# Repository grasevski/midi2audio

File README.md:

# midiguitar
Guitar midi controller + audio interface using an STM32H743ZI

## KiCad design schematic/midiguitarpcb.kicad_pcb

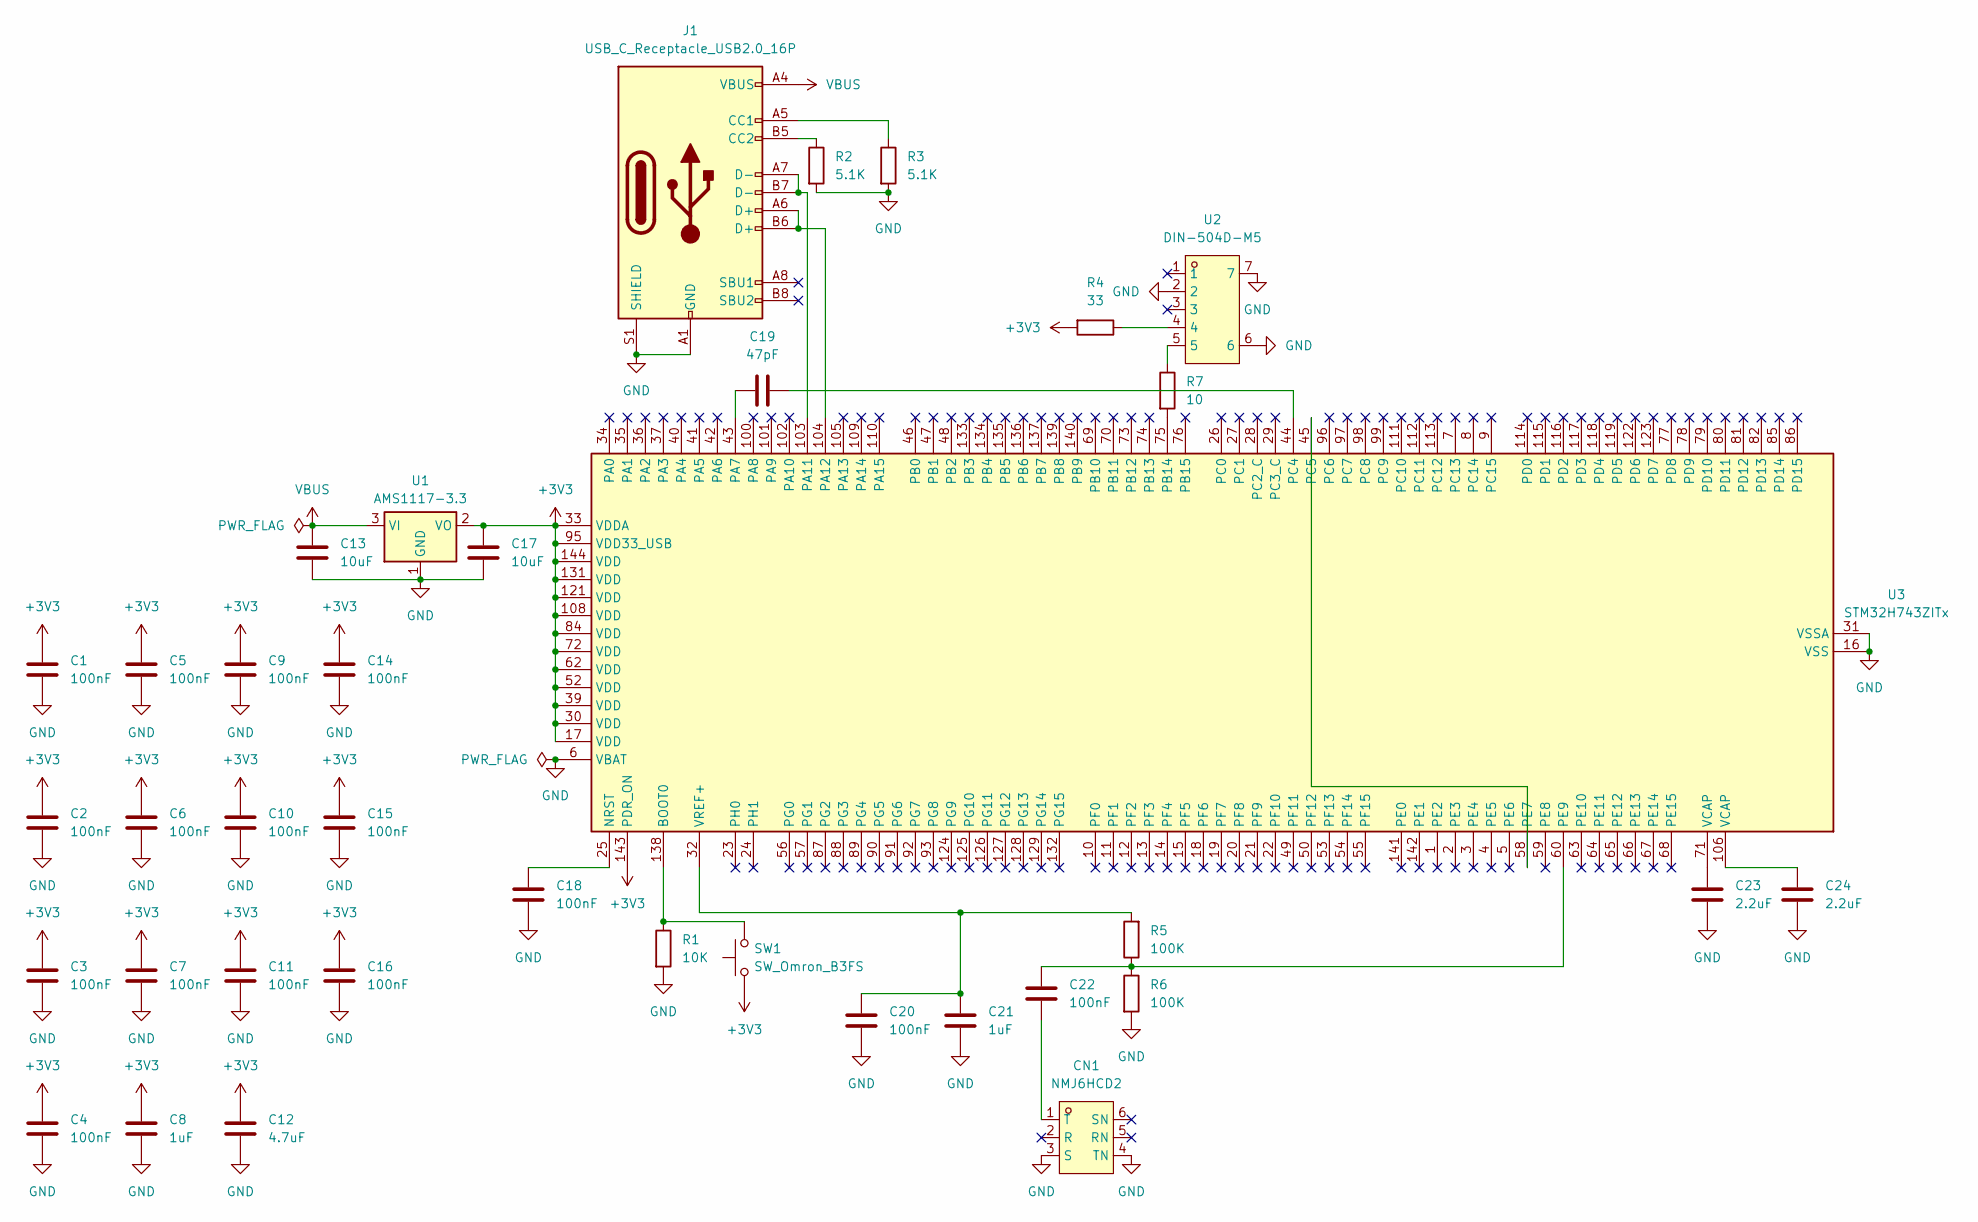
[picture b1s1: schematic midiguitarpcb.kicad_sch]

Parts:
C1, C2, C3, C4, C5, C6, C7, C9, C10, C11, C14, C15, C16, C18, C20, C22: 100nF; C_0402_1005Metric
C8, C21: 1uF; C_0402_1005Metric
C12: 4.7uF; C_0402_1005Metric
C13, C17: 10uF; C_0402_1005Metric
C19: 47pF; C_0402_1005Metric
C23, C24: 2.2uF; C_0402_1005Metric
CN1: NMJ6HCD2; AUDIO-TH_NMJ6HCD2; LCSC Part C368502
J1: USB_C_Receptacle_USB2.0_16P; USB_C_Receptacle_HRO_TYPE-C-31-M-12
R1: 10K; R_0402_1005Metric
R2, R3: 5.1K; R_0402_1005Metric
R4: 33; R_0402_1005Metric
R5, R6: 100K; R_0402_1005Metric
R7: 10; R_0402_1005Metric
SW1: SW_Omron_B3FS; SW_SPST_Omron_B3FS-100xP
U1: AMS1117-3.3; SOT-223-3_TabPin2
U2: DIN-504D-M5; CONN-TH_DIN-504D-M5; LCSC Part C2939347
U3: STM32H743ZITx; LQFP-144_20x20mm_P0.5mm

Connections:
+3V3: C1.1, C2.1, C3.1, C4.1, C5.1, C6.1, C7.1, C8.1, C9.1, C10.1, C11.1, C12.1, C14.1, C15.1, C16.1, C17.1, R4.2, SW1.1, U1.2 (VO), U3.17 (VDD), U3.30 (VDD), U3.33 (VDDA), U3.39 (VDD), U3.52 (VDD), U3.62 (VDD), U3.72 (VDD), U3.84 (VDD), U3.95 (VDD33_USB), U3.108 (VDD), U3.121 (VDD), U3.131 (VDD), U3.143 (PDR_ON), U3.144 (VDD)
GND: C1.2, C2.2, C3.2, C4.2, C5.2, C6.2, C7.2, C8.2, C9.2, C10.2, C11.2, C12.2, C13.2, C14.2, C15.2, C16.2, C17.2, C18.2, C20.2, C21.2, C23.2, C24.2, CN1.3 (S), CN1.4 (TN), J1.A1 (GND), J1.A12 (GND), J1.B1 (GND), J1.B12 (GND), J1.S1 (SHIELD), R1.2, R2.2, R3.2, R6.2, U1.1 (GND), U2.2, U2.6, U2.7, U3.6 (VBAT), U3.16 (VSS), U3.31 (VSSA), U3.38 (VSS), U3.51 (VSS), U3.61 (VSS), U3.83 (VSS), U3.94 (VSS), U3.107 (VSS), U3.120 (VSS), U3.130 (VSS)
unnamed: C23.1, U3.71 (VCAP)
unnamed: C24.1, U3.106 (VCAP)
unnamed: C22.1, CN1.1 (T)
unnamed: J1.A5 (CC1), R3.1
unnamed: J1.B5 (CC2), R2.1
unnamed: R4.1, U2.4
unnamed: R7.1, U2.5
unnamed: R1.1, SW1.2, U3.138 (BOOT0)
unnamed: C18.1, U3.25 (NRST)
unnamed: C19.1, U3.43 (PA7)
unnamed: J1.A7 (D-), J1.B7 (D-), U3.103 (PA11)
unnamed: J1.A6 (D+), J1.B6 (D+), U3.104 (PA12)
unnamed: R7.2, U3.75 (PB14)
unnamed: C19.2, U3.44 (PC4)
unnamed: U3.45 (PC5), U3.58 (PE7)
unnamed: C22.2, R5.1, R6.1, U3.60 (PE9)
unnamed: C20.1, C21.1, R5.2, U3.32 (VREF+)
VBUS: C13.1, J1.A4 (VBUS), J1.A9 (VBUS), J1.B4 (VBUS), J1.B9 (VBUS), U1.3 (VI)

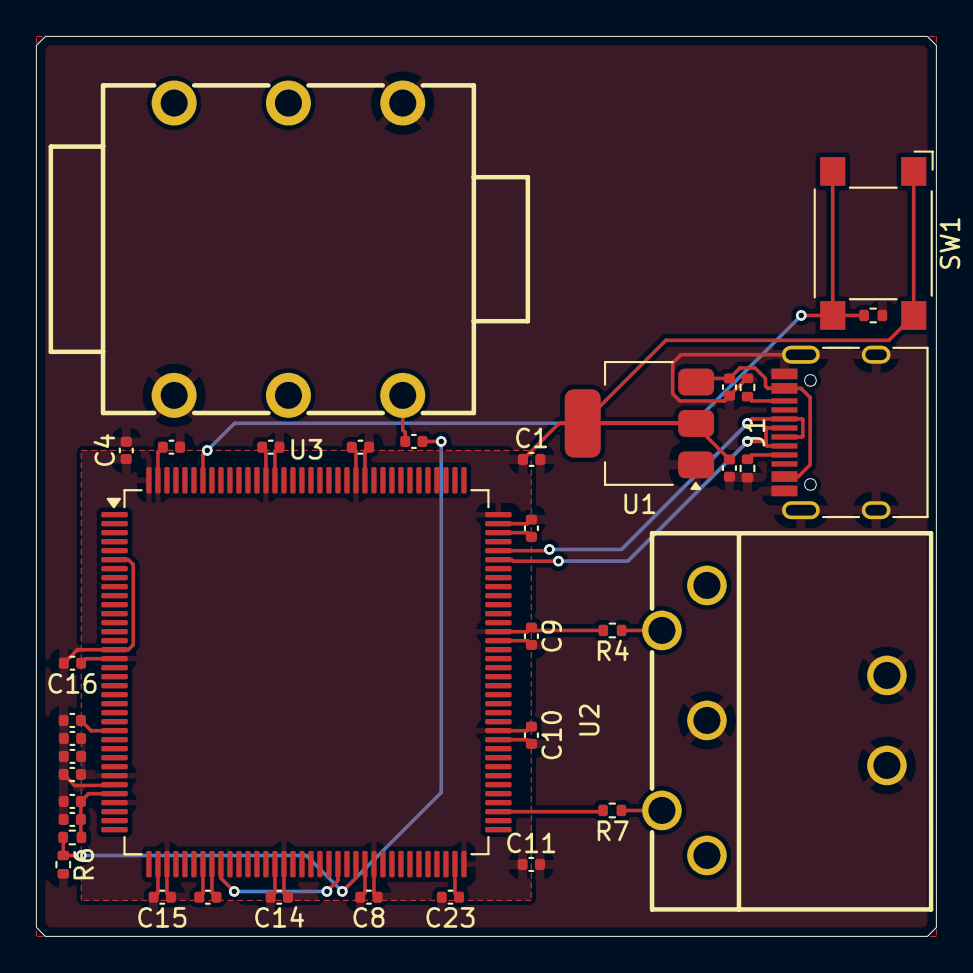
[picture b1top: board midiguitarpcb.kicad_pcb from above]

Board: 2 copper layers, 50.0 x 50.0 mm, 37 parts (0 on the bottom side), 20 nets.

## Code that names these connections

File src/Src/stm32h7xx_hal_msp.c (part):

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
    __HAL_RCC_GPIOC_CLK_ENABLE();
    /**ADC1 GPIO Configuration
    PC4     ------> ADC1_INP4
    */
    GPIO_InitStruct.Pin = GPIO_PIN_4;
    GPIO_InitStruct.Mode = GPIO_MODE_ANALOG;
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    __HAL_RCC_ADC12_CLK_DISABLE();

    /**ADC1 GPIO Configuration
    PC4     ------> ADC1_INP4
    */
    HAL_GPIO_DeInit(GPIOC, GPIO_PIN_4);

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    __HAL_RCC_GPIOC_CLK_ENABLE();
    __HAL_RCC_GPIOB_CLK_ENABLE();
    /**OPAMP1 GPIO Configuration
    PA7     ------> OPAMP1_VINM1
    PC4     ------> OPAMP1_VOUT
    PC5     ------> OPAMP1_VINM0
    PB0     ------> OPAMP1_VINP
    */
    GPIO_InitStruct.Pin = GPIO_PIN_7;
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
    __HAL_RCC_GPIOE_CLK_ENABLE();
    /**OPAMP2 GPIO Configuration
    PE7     ------> OPAMP2_VOUT
    PE9     ------> OPAMP2_VINP
    */
    GPIO_InitStruct.Pin = GPIO_PIN_7|GPIO_PIN_9;
    GPIO_InitStruct.Mode = GPIO_MODE_ANALOG;
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    }

    /**OPAMP1 GPIO Configuration
    PA7     ------> OPAMP1_VINM1
    PC4     ------> OPAMP1_VOUT
    PC5     ------> OPAMP1_VINM0
    PB0     ------> OPAMP1_VINP
    */
    HAL_GPIO_DeInit(GPIOA, GPIO_PIN_7);
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    }

    /**OPAMP2 GPIO Configuration
    PE7     ------> OPAMP2_VOUT
    PE9     ------> OPAMP2_VINP
    */
    HAL_GPIO_DeInit(GPIOE, GPIO_PIN_7|GPIO_PIN_9);

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
    __HAL_RCC_GPIOB_CLK_ENABLE();
    /**USART1 GPIO Configuration
    PB14     ------> USART1_TX
    */
    GPIO_InitStruct.Pin = GPIO_PIN_14;
    GPIO_InitStruct.Mode = GPIO_MODE_AF_OD;
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    __HAL_RCC_USART1_CLK_DISABLE();

    /**USART1 GPIO Configuration
    PB14     ------> USART1_TX
    */
    HAL_GPIO_DeInit(GPIOB, GPIO_PIN_14);

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
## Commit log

2022-03-03 Add code
2022-03-11 WIP about to try lo fi dac
2022-03-16 WIP got it working
2022-03-17 update circuit
2022-03-17 cleanup
2022-03-18 undo mistake changes
2022-04-02 ready to do midi controller (or wavetable synth)
2022-04-21 WIP about to refactor to facilitate unit testing
2022-04-26 code complete
2022-04-26 fix pitch offset
2022-04-26 fix up pitches
2022-04-27 formatting
2022-04-28 simplify
2022-05-30 [WIP] midi controller is working, but only to semitone resolution
2022-06-04 tests passing, but program not building
2022-06-04 everything compiles and passes tests
2022-06-06 fuzz test
2022-06-11 reduce memory usage
2022-06-11 reduce memory usage more
2022-06-11 28KB total flash memory usage
2022-06-18 increased wavelength resolution, pitch bending works now
2022-06-18 more cleanup
2022-07-02 make input and output both 8 bit
2022-08-03 chore: update readme
2022-08-04 wip: stm32
2022-08-04 fix: change to l432
2023-03-05 feat(stm): migrated
2023-03-10 fix(cfg): panic halt
2023-04-02 fix(integration): tested on stm32
2023-04-02 chore(build): compile in release mode
2023-04-02 Revert "chore(build): compile in release mode"
    This reverts commit e595cc4ed3eeb5c67f61b94baf44d4b2386250f0.
2023-04-05 chore(wip): read midi without dma
2023-04-05 chore(buffer): resize
2023-04-11 chore(testing): monophonic version done
2024-01-05 wip generating lookup
2024-01-05 wip fastf0nls
2024-02-02 feat(pitch): fastf0nls code complete
2024-02-03 fix(dma): reorder operations
2024-03-19 feat(stm32): implemented dma drivers
2024-03-20 chore(debug): remove logging
2024-07-07 feat(rewrite): RiiC
2024-07-27 chore(wip): about to remove usb code
2024-07-27 chore(usb): remove
2024-08-01 fix(integration): tested on host
2024-08-04 fix(pcb): midi resistors swapped
2024-08-11 wip(usb): about to discard tinyusb
2024-08-12 feat(stm32h7): done
2024-08-13 chore(pcb): update
2024-08-27 feat(schematic): redo with 2nd opamp

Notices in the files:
src/Src/stm32h7xx_hal_msp.c:
Copyright (c) 2024 STMicroelectronics.
All rights reserved.
This software is licensed under terms that can be found in the LICENSE file
